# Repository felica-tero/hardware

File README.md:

# hardware
board design projects

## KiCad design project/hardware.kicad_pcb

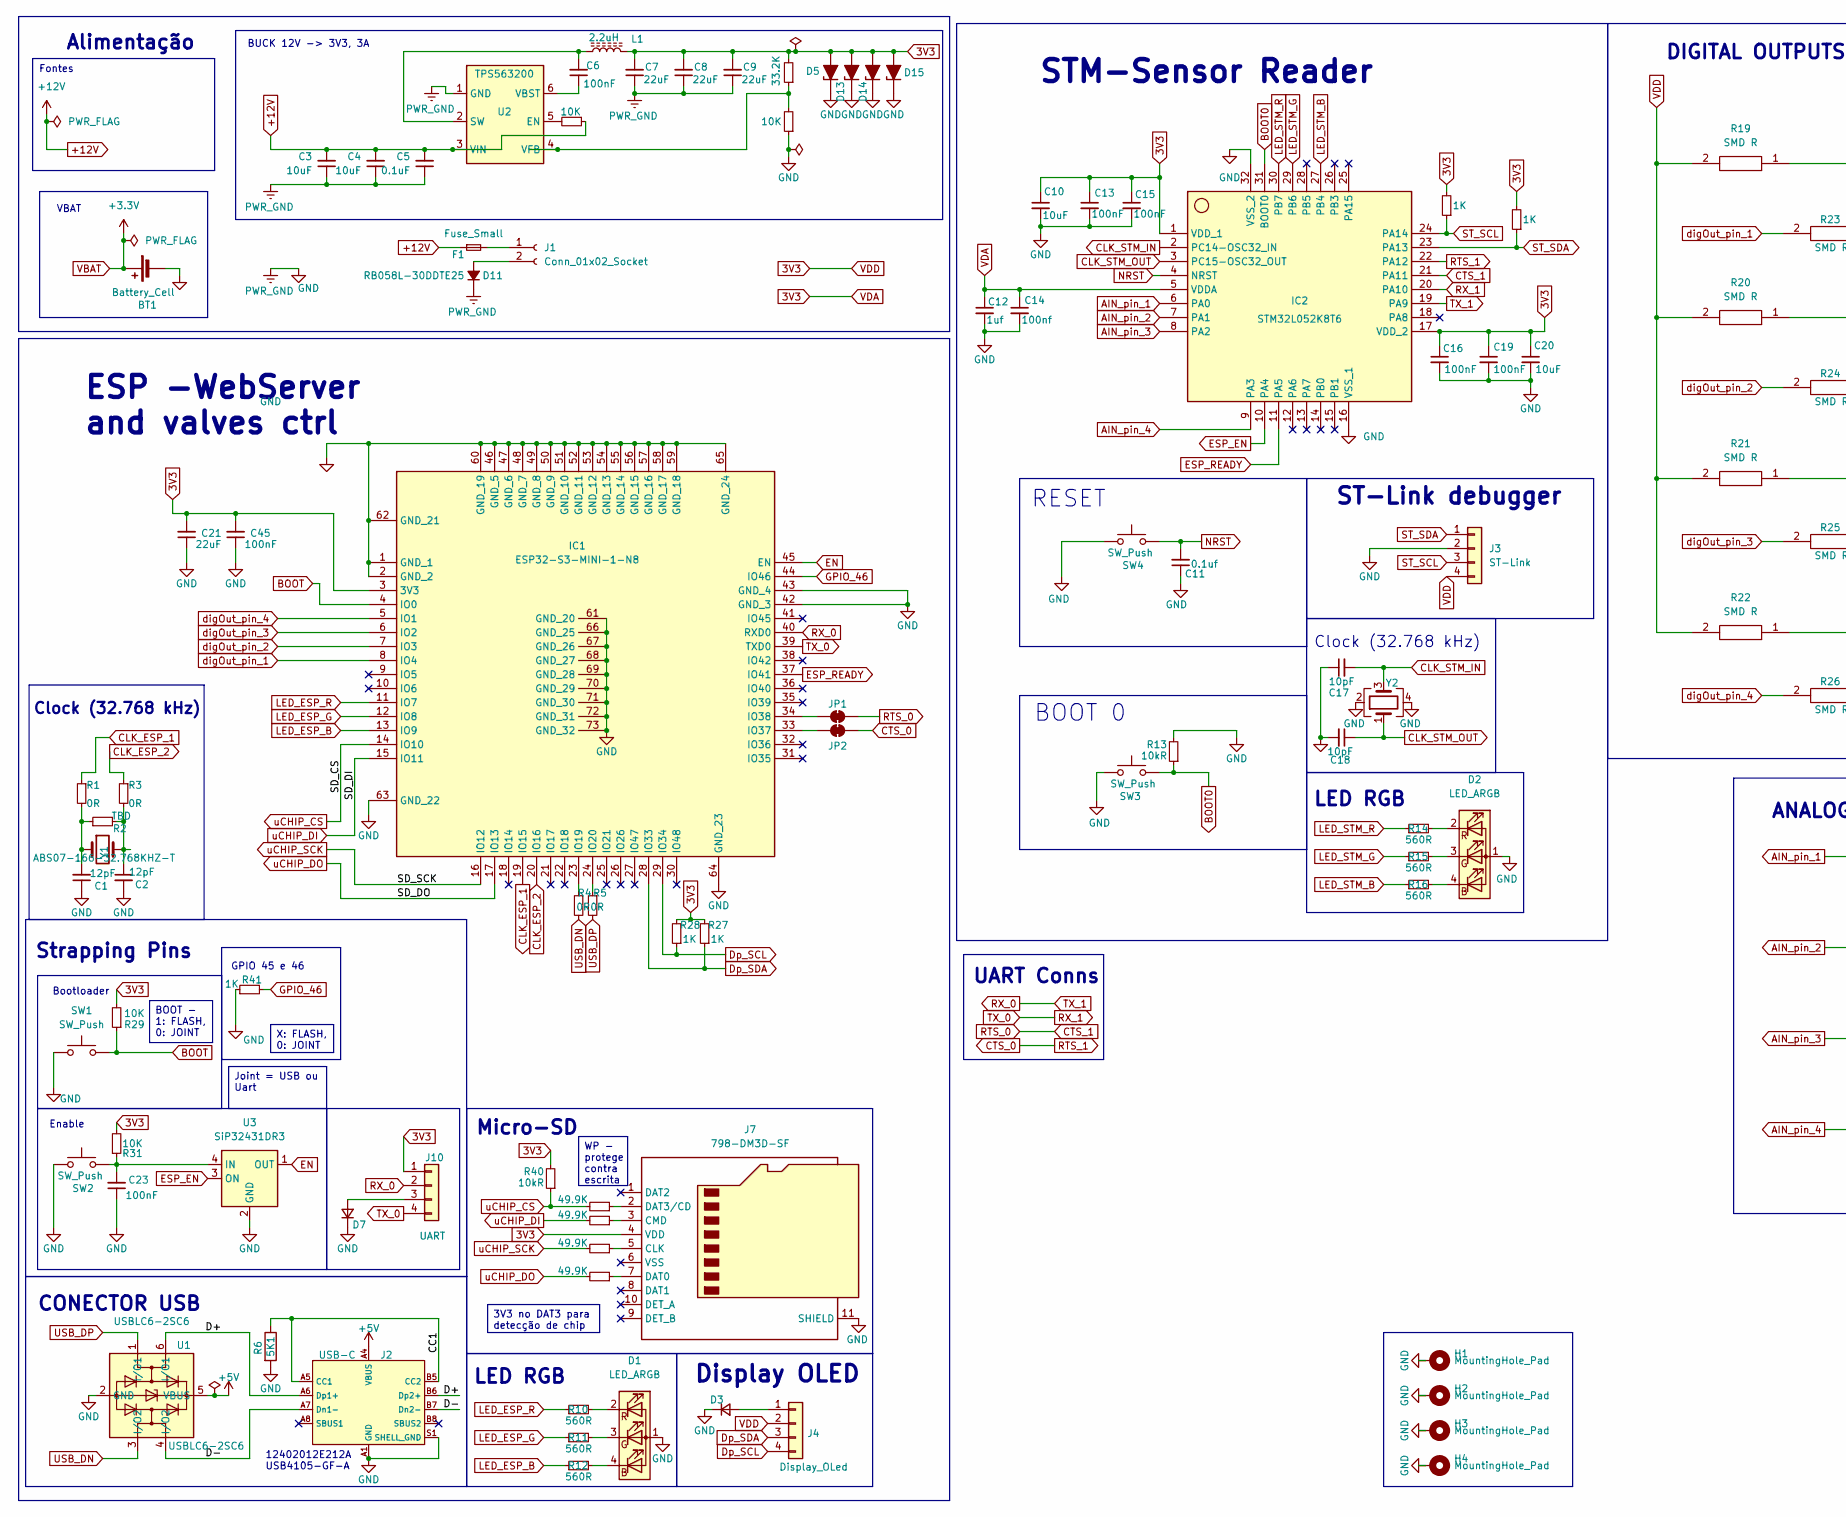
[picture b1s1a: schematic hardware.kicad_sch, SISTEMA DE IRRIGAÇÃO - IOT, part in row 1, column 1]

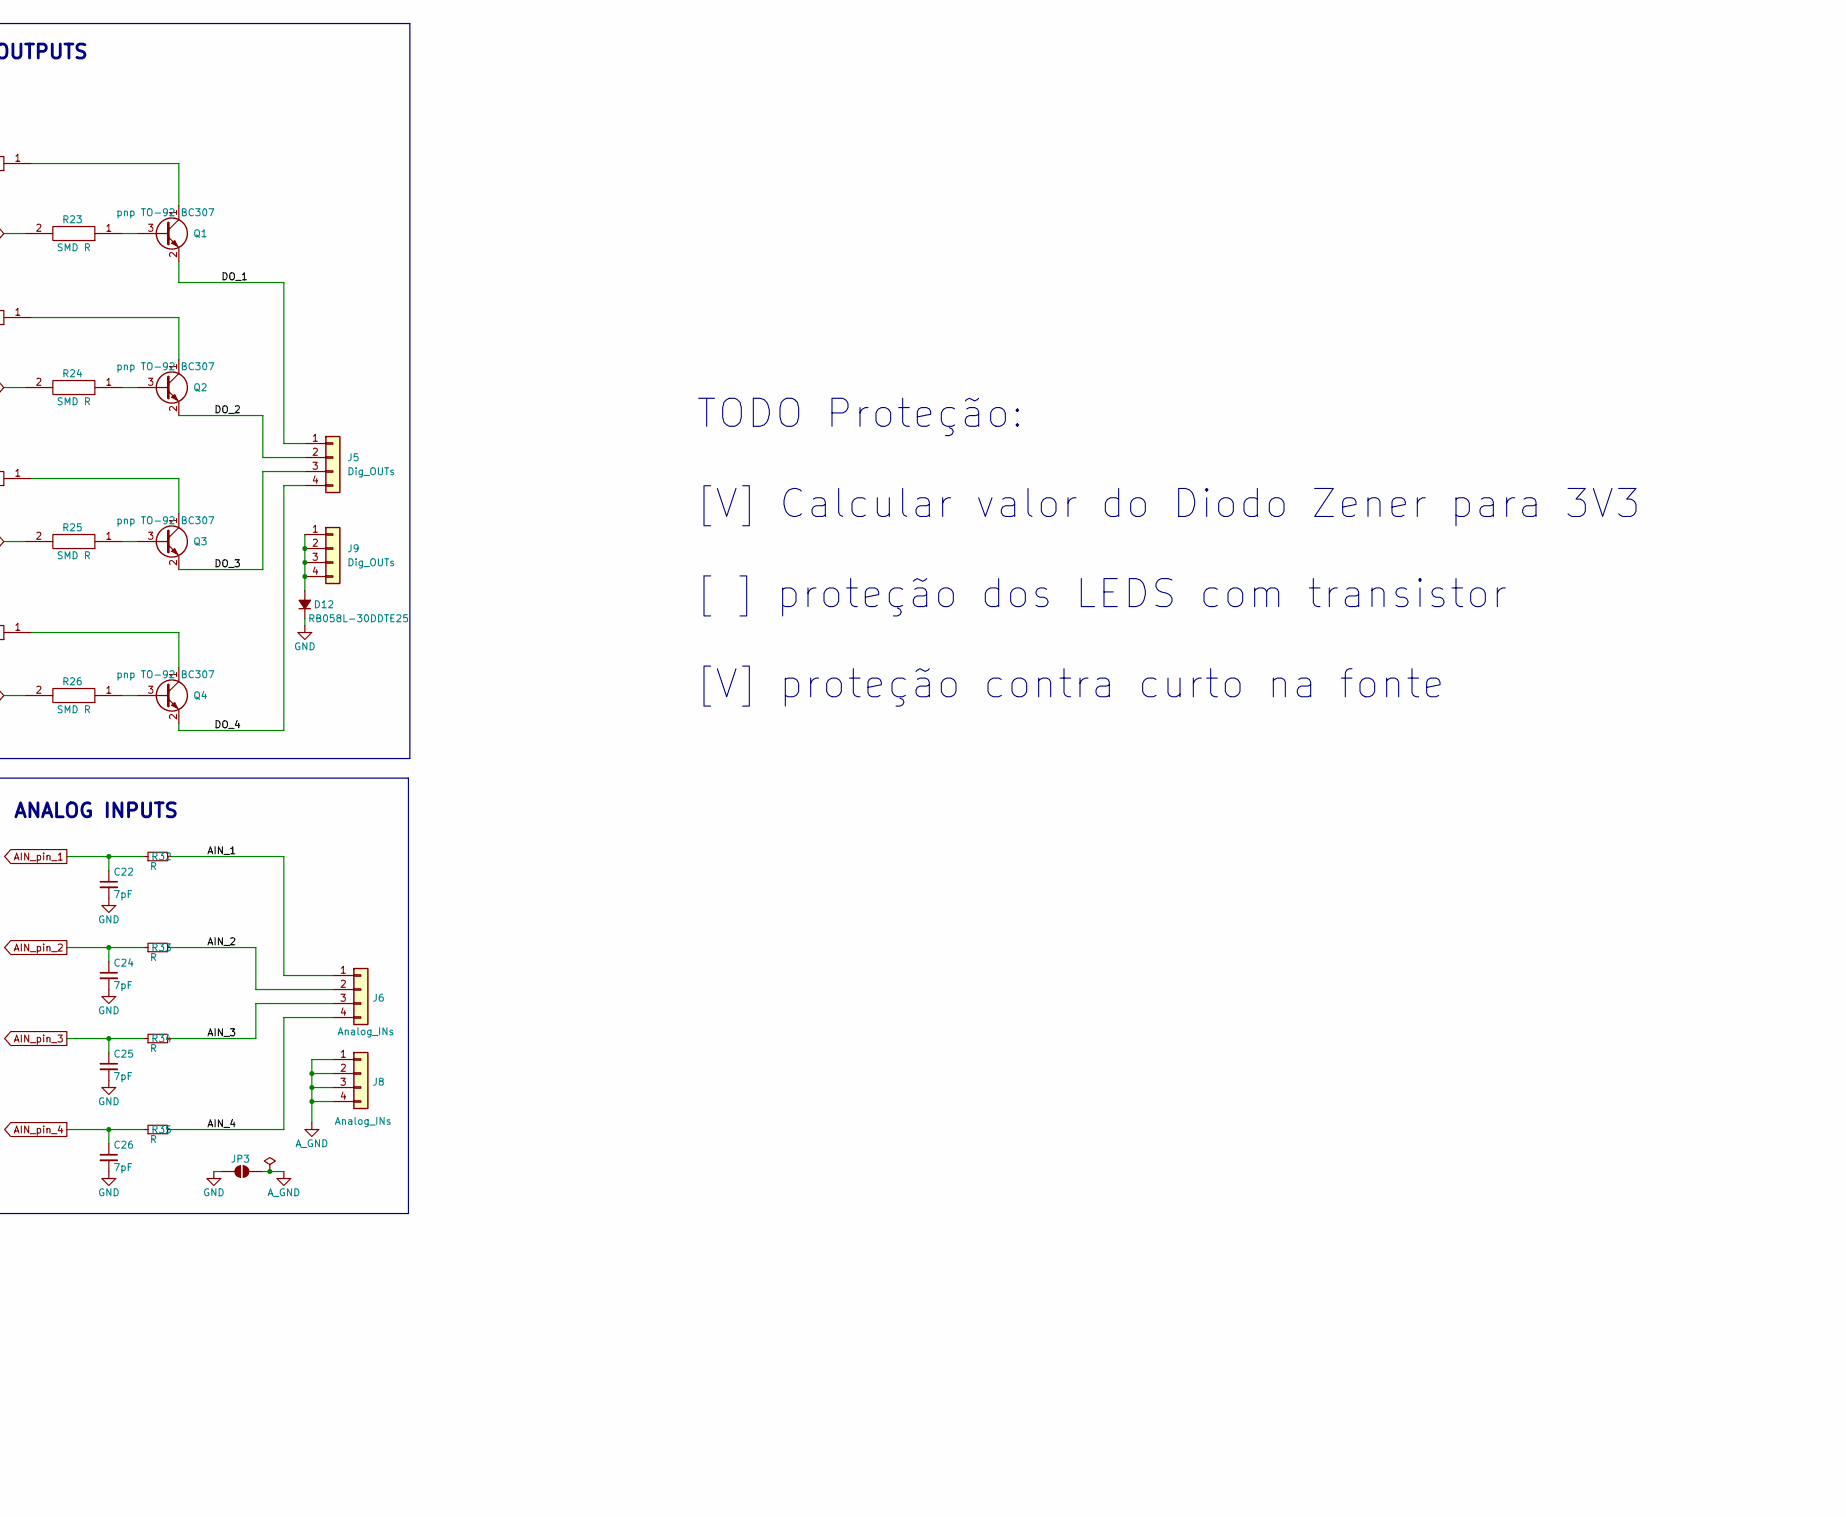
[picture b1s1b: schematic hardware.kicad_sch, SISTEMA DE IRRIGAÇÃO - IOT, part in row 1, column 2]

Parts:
BT1: Battery_Cell
C1, C2: 12pF; C_0402_1005Metric
C3, C4: 10uF; C_0805_2012Metric_Pad1.18x1.45mm_HandSolder
C5: 0.1uF; C_0402_1005Metric_Pad0.74x0.62mm_HandSolder
C6: 100nF; C_0805_2012Metric_Pad1.18x1.45mm_HandSolder
C7, C8, C9: 22uF; C_0603_1608Metric_Pad1.08x0.95mm_HandSolder
C10, C20: 10uF; C_0603_1608Metric; LCSC Part # C19666
C11: 0.1uf; C_0603_1608Metric; LCSC Part # C15195
C12: 1uf; C_0603_1608Metric; LCSC Part # C52923
C13, C15, C16, C19: 100nF; C_0603_1608Metric; LCSC Part # C1525
C14: 100nf; C_0603_1608Metric; LCSC Part # C15195
C17, C18: 10pF; C_0402_1005Metric
C21: 22uF; C_0402_1005Metric
C22, C24, C25, C26: 7pF; C_0603_1608Metric; LCSC Part # C1525
C23, C45: 100nF; C_0402_1005Metric
D1, D2: LED_ARGB; PinSocket_1x04_P1.27mm_Vertical
D3, D7: CDBQR42/43-HF; D_0402_1005Metric
D5, D13, D14, D15: D_Zener_Filled; D_SOD-123; Mouser Part Number 78-MMSZ5226CHE3_A-08
D11, D12: RB058L-30DDTE25; DIOM5026X220N; Mouser Part Number 755-RB058L-30DDTE25
F1: Fuse_Small; Fuse_1206_3216Metric; Mouser Part Number 652-SF-1206HIA050M-2
H1, H2, H3, H4: MountingHole_Pad; MountingHole_4.3mm_M4_Pad_Via
IC1: ESP32-S3-MINI-1-N8; ESP32S3MINI1N8; Mouser Part Number 356-ESP32-S3-MINI1N8
IC2: STM32L052K8T6; LQFP-32_7x7mm_P0.8mm; Manufacturer_Part_Number STM32L052K8T6; Mouser Part Number 511-STM32L052K8T6
J1: Conn_01x02_Socket; Molex_KK-254_AE-6410-02A_1x02_P2.54mm_Vertical
J2: USB-C; USB_C_Receptacle_XKB_U262-16XN-4BVC11
J3: ST-Link; PinSocket_1x04_P2.54mm_Vertical
J4: Display_OLed; Molex_PicoBlade_53048-0410_1x04_P1.25mm_Horizontal
J5, J9: Dig_OUTs; TerminalBlock_bornier-4_P5.08mm
J6, J8: Analog_INs; Molex_PicoBlade_53048-0410_1x04_P1.25mm_Horizontal
J7: 798-DM3D-SF; microSD_HC_Hirose_DM3D-SF; Mouser Part Number 523-GMC020080HR
J10: UART; PinSocket_1x04_P2.54mm_Vertical
JP1, JP2: SolderJumper_2_Bridged; SolderJumper-2_P1.3mm_Bridged_RoundedPad1.0x1.5mm
JP3: SolderJumper_2_Open; SolderJumper-2_P1.3mm_Open_RoundedPad1.0x1.5mm
L1: 2.2uH; L_TDK_VLS6045EX_VLS6045AF
Q1, Q2, Q3, Q4: pnp TO-92 BC307; TO-92_Inline; Manufacturer_Part_Number NTD4858N-35G; Mouser Part Number 863-NTD4858N-35G
R1, R3, R4, R5: 0R; R_0402_1005Metric
R2: TBD; R_0402_1005Metric
R6: 5K1; R_0402_1005Metric
R7, R9, R31: 10K; R_0603_1608Metric_Pad0.98x0.95mm_HandSolder
R8: 33.2K; R_0402_1005Metric_Pad0.72x0.64mm_HandSolder
R10, R11, R12, R14, R15, R16: 560R; R_0402_1005Metric
R13, R40: 10kR; R_0603_1608Metric_Pad0.98x0.95mm_HandSolder; LCSC Part # C25744
R17, R18: 1K; R_0402_1005Metric_Pad0.72x0.64mm_HandSolder
R19, R20, R21, R22, R23, R24, R25, R26: SMD R; R_0603_1608Metric_Pad0.98x0.95mm_HandSolder; Manufacturer_Part_Number CR0603-JW-221ELF; Mouser Part Number 652-CR0603-JW-221ELF
R27, R28, R41: 1K; R_0402_1005Metric
R29: 10K; R_0402_1005Metric
R32, R33, R34, R35: R; R_0402_1005Metric
R36, R37, R38, R39: 49.9K; R_0402_1005Metric
SW1, SW2, SW3, SW4: SW_Push; SW_SPST_PTS810
U1: USBLC6-2SC6; SOT95P280X145-6N
U2: TPS563200; SOT-23-6_Handsoldering
U3: SiP32431DR3; SOT-363_SC-70-6
Y1: ABS07-166-32.768KHZ-T; Crystal_SMD_MicroCrystal_CC7V-T1A-2Pin_3.2x1.5mm_HandSolder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
Y2: ECS-400-10-36B2-CKM-TR; Crystal_SMD_2520-4Pin_2.5x2.0mm

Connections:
3V3: C7.2, C8.2, C9.2, C10.1, C12.1, C13.1, C14.1, C15.1, C16.1, C19.1, C20.1, C21.2, C45.2, D5.2 (A), D13.2 (A), D14.2 (A), D15.2 (A), IC1.3 (3V3), IC2.1 (VDD_1), IC2.5 (VDDA), IC2.17 (VDD_2), J3.4 (VCC), J4.2 (VCC), J7.4 (VDD), J10.1 (SWDIO), L1.2, R8.2, R17.2, R18.2, R19.2, R20.2, R21.2, R22.2, R27.2, R28.2, R29.2, R31.2, R40.2
+5V: J2.A4 (VBUS), J2.A9 (VBUS), J2.B4 (VBUS), J2.B9 (VBUS), U1.5 (VBUS)
+12V: C3.2, C4.2, C5.2, F1.1, R7.1, U2.3 (VIN)
/AIN_1: J6.1, R32.2
/AIN_2: J6.2, R33.2
/AIN_3: J6.3, R34.2
/AIN_4: J6.4, R35.2
/CC1: J2.A5 (CC1), J2.B5 (CC2), R6.1
/D+: J2.A6 (Dp1+), J2.B6 (Dp2+), U1.6 (I/O1)
/D-: J2.A7 (Dn1-), J2.B7 (Dn2-), U1.4 (I/O2)
/DO_1: J5.1, Q1.2 (E)
/DO_2: J5.2, Q2.2 (E)
/DO_3: J5.3, Q3.2 (E)
/DO_4: J5.4, Q4.2 (E)
AIN_pin_1: C22.1, IC2.6 (PA0), R32.1
AIN_pin_2: C24.1, IC2.7 (PA1), R33.1
AIN_pin_3: C25.1, IC2.8 (PA2), R34.1
AIN_pin_4: C26.1, IC2.9 (PA3), R35.1
A_GND: J8.1, J8.2, J8.3, J8.4, JP3.2 (B)
BOOT: IC1.4 (IO0), R29.1, SW1.2
BOOT0: IC2.31 (BOOT0), R13.1, SW3.1
CLK_ESP_1: IC1.19 (IO15), R1.1
CLK_ESP_2: IC1.20 (IO16), R3.1
CLK_STM_IN: C17.2, IC2.2 (PC14-OSC32_IN), Y2.3
CLK_STM_OUT: C18.1, IC2.3 (PC15-OSC32_OUT), Y2.1
CTS_0: IC2.22 (PA12), JP2.2 (B)
CTS_1: IC2.21 (PA11), JP1.2 (B)
Dp_SCL: IC1.29 (IO34), J4.4 (SDA), R28.1
Dp_SDA: IC1.28 (IO33), J4.3 (SCL), R27.1
EN: IC1.45 (EN), U3.1 (OUT)
ESP_EN: IC2.10 (PA4), U3.3 (ON)
ESP_READY: IC1.37 (IO41), IC2.11 (PA5)
GND: BT1.2 (-), C1.1, C2.2, C3.1, C4.1, C5.1, C7.1, C8.1, C9.1, C10.2, C11.1, C12.2, C13.2, C14.2, C15.2, C16.2, C17.1, C18.2, C19.2, C20.2, C21.1, C22.2, C23.1, C24.2, C25.2, C26.2, C45.1, D1.1 (A), D2.1 (A), D3.1 (K), D5.1 (K), D7.1 (K), D11.1 (K), D12.1 (K), D13.1 (K), D14.1 (K), D15.1 (K), H1.1 (1_1), H2.1 (1_1), H3.1 (1_1), H4.1 (1_1), IC1.1 (GND_1), IC1.2 (GND_2), IC1.42 (GND_3), IC1.43 (GND_4), IC1.46 (GND_5), IC1.47 (GND_6), IC1.48 (GND_7), IC1.49 (GND_8), IC1.50 (GND_9), IC1.51 (GND_10), IC1.52 (GND_11), IC1.53 (GND_12), IC1.54 (GND_13), IC1.55 (GND_14), IC1.56 (GND_15), IC1.57 (GND_16), IC1.58 (GND_17), IC1.59 (GND_18), IC1.60 (GND_19), IC1.61 (GND_20), IC1.62 (GND_21), IC1.63 (GND_22), IC1.64 (GND_23), IC1.65 (GND_24), IC1.66 (GND_25), IC1.67 (GND_26), IC1.68 (GND_27), IC1.69 (GND_28), IC1.70 (GND_29), IC1.71 (GND_30), IC1.72 (GND_31), IC1.73 (GND_32), IC2.16 (VSS_1), IC2.32 (VSS_2), J2.A1 (GND), J2.A12 (GND), J2.B1 (GND), J2.B12 (GND), J2.S1 (SHELL_GND), J3.2 (GND), J7.11 (SHIELD), JP3.1 (A), R6.2, R9.1, R13.2, R41.1, SW1.1, SW2.1, SW3.2, SW4.1, U1.2 (GND), U2.1 (GND), U3.2 (GND), U3.5 (GND), Y2.2, Y2.4
GPIO_46: IC1.44 (IO46), R41.2
LED_ESP_B: IC1.13 (IO9), R12.1
LED_ESP_G: IC1.12 (IO8), R11.1
LED_ESP_R: IC1.11 (IO7), R10.1
LED_STM_B: IC2.27 (PB4), R16.1
LED_STM_G: IC2.29 (PB6), R15.1
LED_STM_R: IC2.30 (PB7), R14.1
NRST: C11.2, IC2.4 (NRST), SW4.2
unnamed: C1.2, R1.2, R2.1, Y1.1
unnamed: C2.1, R2.2, R3.2, Y1.2
unnamed: D1.4 (BK), R12.2
unnamed: D1.3 (GK), R11.2
unnamed: D1.2 (RK), R10.2
unnamed: D2.4 (BK), R16.2
unnamed: D2.3 (GK), R15.2
unnamed: D2.2 (RK), R14.2
unnamed: D3.2 (A), J4.1 (GND)
unnamed: D7.2 (A), J10.3 (SWCLK)
unnamed: D11.2 (A), J1.2
unnamed: D12.2 (A), J9.1, J9.2, J9.3, J9.4
unnamed: IC1.23 (IO19), R4.1
unnamed: IC1.24 (IO20), R5.1
unnamed: IC1.33 (IO37), JP2.1 (A)
unnamed: IC1.34 (IO38), JP1.1 (A)
unnamed: F1.2, J1.1
unnamed: J7.5 (CLK), R37.1
unnamed: J7.3 (CMD), R38.1
unnamed: J7.7 (DAT0), R39.1
unnamed: J7.2 (DAT3/CD), R36.1
unnamed: Q1.3 (B), R23.1
unnamed: Q1.1 (C), R19.1
unnamed: Q2.3 (B), R24.1
unnamed: Q2.1 (C), R20.1
unnamed: Q3.3 (B), R25.1
unnamed: Q3.1 (C), R21.1
unnamed: Q4.3 (B), R26.1
unnamed: Q4.1 (C), R22.1
unnamed: R7.2, U2.5 (EN)
unnamed: C6.2, L1.1, U2.2 (SW)
unnamed: C6.1, U2.6 (VBST)
unnamed: R8.1, R9.2, U2.4 (VFB)
unnamed: C23.2, R31.1, SW2.2, U3.4 (IN)
RX_0: IC1.40 (RXD0), IC2.19 (PA9), J10.2 (GND)
RX_1: IC1.39 (TXD0), IC2.20 (PA10), J10.4 (VCC)
ST_SCL: IC2.24 (PA14), J3.3 (SWCLK), R17.1
ST_SDA: IC2.23 (PA13), J3.1 (SWDIO), R18.1
USB_DN: R4.2, U1.3 (I/O2)
USB_DP: R5.2, U1.1 (I/O1)
digOut_pin_1: IC1.8 (IO4), R23.2
digOut_pin_2: IC1.7 (IO3), R24.2
digOut_pin_3: IC1.6 (IO2), R25.2
digOut_pin_4: IC1.5 (IO1), R26.2
uCHIP_CS: IC1.14 (IO10), R36.2, R40.1
uCHIP_DI: IC1.15 (IO11), R38.2
uCHIP_DO: IC1.17 (IO13), R39.2
uCHIP_SCK: IC1.16 (IO12), R37.2

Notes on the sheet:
Clock (32.768 kHz)
Strapping Pins
LED RGB
ESP -WebServer and valves ctrl
Enable
Bootloader
RESET
Micro-SD
CONECTOR USB
VBAT
GPIO 45 e 46
ST-Link debugger
TODO Proteção: [V] Calcular valor do Diodo Zener para 3V3 [ ] proteção dos LEDS com transistor [V] proteção contra curto na fonte
BUCK 12V -> 3V3, 3A
12402012E212A USB4105-GF-A
STM-Sensor Reader
Alimentação
BOOT 0
UART Conns
Display OLED
DIGITAL OUTPUTS
ANALOG INPUTS
Fontes
Joint = USB ou Uart
X: FLASH, 0: JOINT
3V3 no DAT3 para detecção de chip
WP - protege contra escrita
BOOT - 1: FLASH, 0: JOINT

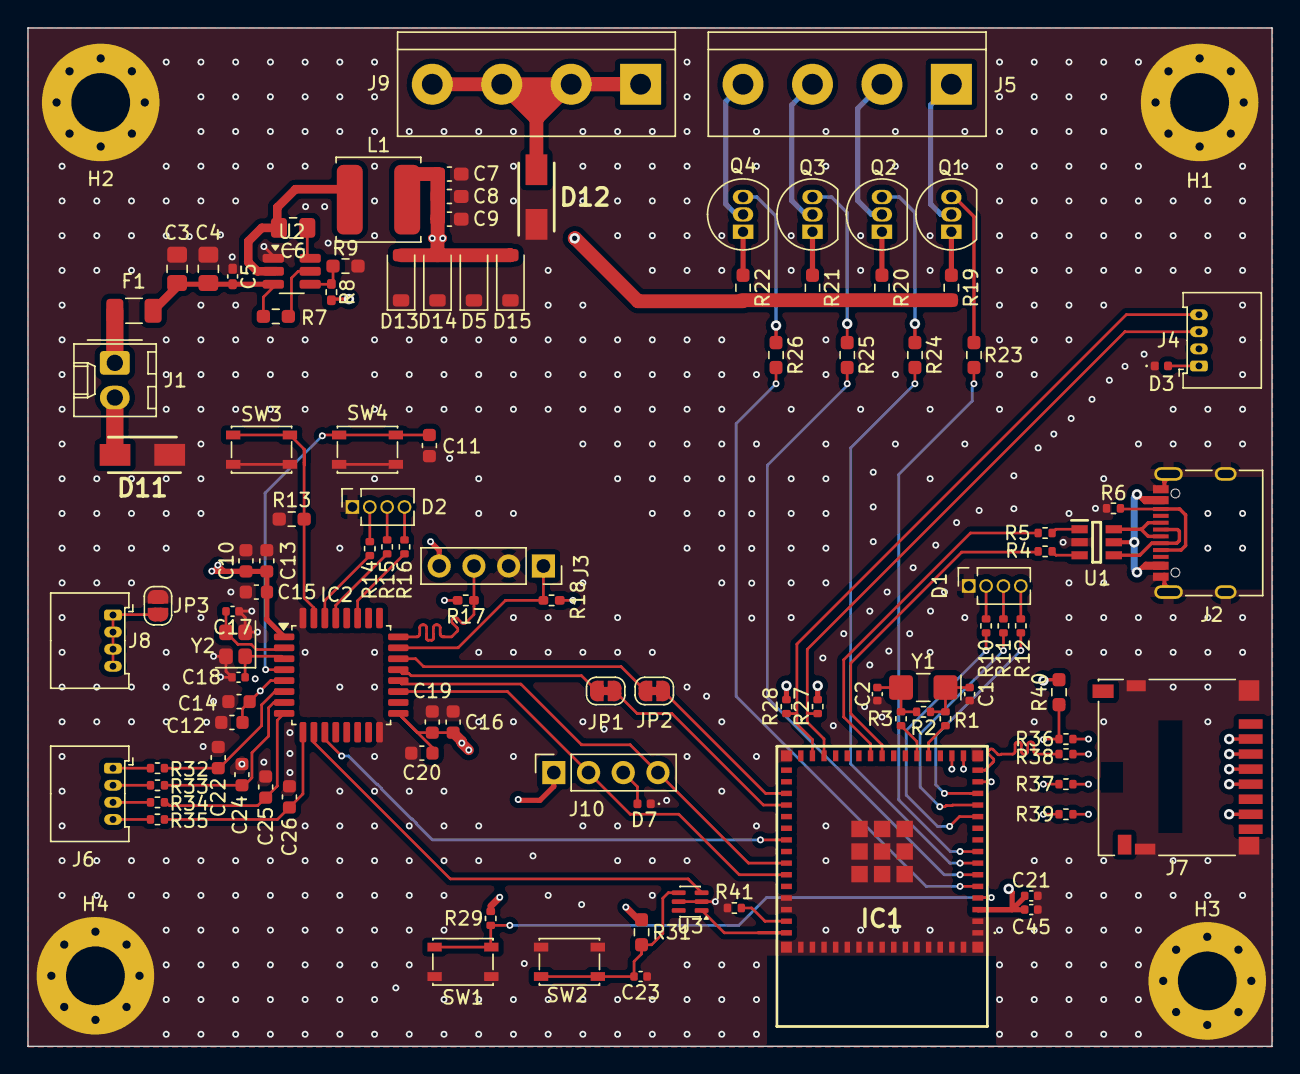
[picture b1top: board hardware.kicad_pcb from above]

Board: 4 copper layers, 91.0 x 74.5 mm, 111 parts (0 on the bottom side), 89 nets.

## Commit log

2025-11-04 schematic v1.0 for MVP
2026-04-19 load switch e esp_ready status
